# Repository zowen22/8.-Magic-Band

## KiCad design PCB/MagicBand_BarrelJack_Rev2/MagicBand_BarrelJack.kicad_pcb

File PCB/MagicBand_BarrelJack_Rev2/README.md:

# MagicBand_BarrelJack — Revision 2

*Created: 2026-10-13. Copied from `PCB/MagicBand_BarrelJack/` (rev 1, fab-ready, two boards fabricated/assembled and in bring-up) — that folder stays untouched/frozen as the as-fabricated reference. This folder is where rev 2 design changes happen.*

Only the KiCad source files were copied (`.kicad_pro/.kicad_sch/.kicad_pcb/.kicad_prl`) — not rev 1's BOM/CPL/gerbers/SVGs/DRC-ERC reports, since those are rev 1-specific fab outputs that would be misleading here until rev 2 actually has changes and gets its own export pass.

## Scope (decided 2026-10-13)

Cleanup pass on the existing wall-powered architecture **plus** a real second-LED-strip connector. **Not** a revisit of the paused battery-powered/IRQ-wake variant — that stays paused pending its own separate decision (see `2. Project Overview.md` Decisions Log, 2026-08-04 entry).

## Backlog — see `3. Work Packages.md` WP4.3 for the authoritative, maintained list

Summary as of creation (check WP4.3 directly for current status, don't trust this snapshot):
1. Silkscreen: per-pin signal labels near J2/J3/J8/J9
2. J6 wire-color documentation/sourcing fix (pigtail kit colors inverted from NeoPixel convention)
3. J6 pin order vs. actual LED strip pad order
4. J8 through-hole size vs. actual barrel-jack wire gauge
5. **New, real connector for second LED strip** (rev 1 only has a hand-bodged wire to U1's D2 leg + a J8 power tap — see `Build Instructions - Barrel-Jack Variant.md` Step 5a — rev 2 should give this its own header + proper trace sizing, not a bodge)
6. +5V trace width to the LED strip(s) — rev 1's 0.2mm trunk sizing was a judgment call, not computed from hard math; revisit with real numbers once rev 2's actual LED part (a new, smaller/lower-draw 2.7mm-width LED, BOM link pending from @user) is confirmed, especially now that it's feeding two strips instead of one
7. RF antenna/J3 keepout — only fix if board 1/2 testing actually shows reduced 433MHz range, don't fix pre-emptively
8. Cosmetic-only: R1/Y1 silkscreen overlap, 3 starved-thermal pour-island flags — bundle in only if doing a placement pass anyway

## What's NOT done yet

No schematic/PCB edits have been made in this folder — it's an exact copy of rev 1 as of 2026-10-13. Placement/routing/silkscreen work in this project has always been a GUI + user session (see `4. Technical Reference.md`'s FreeRouting/placement workflow), not something done headlessly — next step is a live KiCad session against this folder once the second-strip connector's footprint/pin-out is picked.

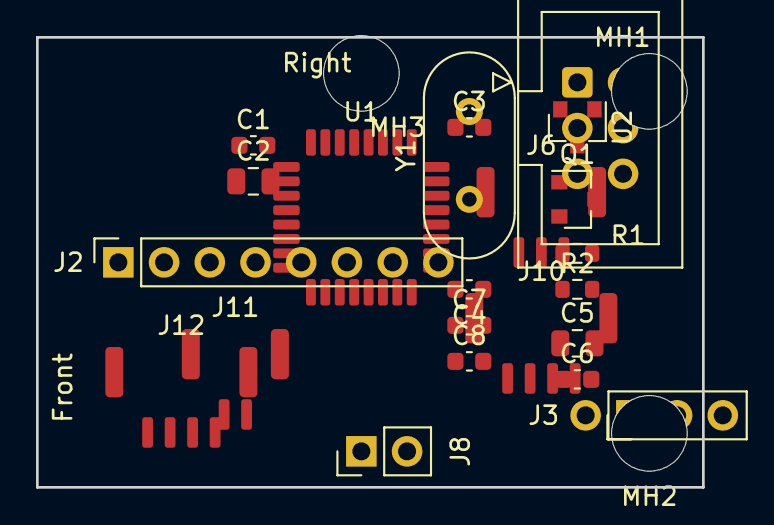
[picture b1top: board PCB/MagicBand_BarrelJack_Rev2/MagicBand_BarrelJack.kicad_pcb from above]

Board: 2 copper layers, 37.0 x 25.0 mm, 25 parts (0 on the bottom side), 22 nets, no tracks yet.

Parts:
C1, C3, C4, C6, C7, C8: C_0603_1608Metric
C2, C5: C_0805_2012Metric
J2: PinSocket_1x08_P2.54mm_Vertical
J3: PinHeader_1x04_P2.54mm_Vertical
J6: LED_OUTER_RING_3P; JST_GH_BM03B-GHS-TBT_1x03-1MP_P1.25mm_Vertical
J8: PinHeader_1x02_P2.54mm_Vertical
J9: IDC-Header_2x03_P2.54mm_Vertical
J10: LED_INNER_RING_4P; JST_GH_BM04B-GHS-TBT_1x04-1MP_P1.25mm_Vertical
J11: SWITCH_2P; JST_GH_BM02B-GHS-TBT_1x02-1MP_P1.25mm_Vertical
J12: SPARE_BREAKOUT_4P; JST_GH_BM04B-GHS-TBT_1x04-1MP_P1.25mm_Vertical
MH1, MH2, MH3: MountingHole_4.2mm
Q1: SOT-23
R1, R2: R_0603_1608Metric
U1: ATmega328P-A; TQFP-32_7x7mm_P0.8mm
U2: SOT-23
Y1: Crystal_HC49-4H_Vertical

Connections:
+3V3: C7.1, J2.8, J3.2, U2.2
+5V: C3.1, C4.1, C5.1, C6.1, J6.1, J9.2, J10.1, Q1.3, R1.1, U1.4, U1.6, U1.18, U2.3
D2: J10.3, U1.32
D4: J2.1, U1.2
D5: J6.3, U1.9
D7: J12.1, U1.11
D8: J3.1, U1.12
D9: J2.7, U1.13
D10: J12.2, U1.14
D11: J2.3, J9.4, U1.15
D12: J2.4, J9.1, U1.16
D13: J2.2, J9.3, U1.17
GND: C1.2, C2.2, C3.2, C4.2, C5.2, C6.2, C7.2, C8.2, J2.6, J3.3, J6.2, J8.2, J9.6, J10.2, J11.2, R2.2, U1.3, U1.5, U1.21, U2.1
MCU_RESET: J9.5, R1.2, U1.29
unnamed: J8.1, Q1.2
unnamed: Q1.1, R2.1
unnamed: C8.1, U1.20
unnamed: C1.1, U1.7, Y1.1
unnamed: C2.1, U1.8, Y1.2
RXD: J12.3, U1.30
SWITCH: J11.1, U1.1
TXD: J12.4, U1.31

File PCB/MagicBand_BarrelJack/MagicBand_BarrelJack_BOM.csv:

"Refs","Value","Footprint","Qty","DNP"
"C1","27pF","Capacitor_SMD:C_0603_1608Metric","1",""
"C2","27pF","Capacitor_SMD:C_0805_2012Metric","1",""
"C3,C4,C8","100nF","Capacitor_SMD:C_0603_1608Metric","3",""
"C5","1uF","Capacitor_SMD:C_0805_2012Metric","1",""
"C6","10uF","Capacitor_SMD:C_0603_1608Metric","1",""
"C7","1.0uF","Capacitor_SMD:C_0603_1608Metric","1",""
"J2","MFRC522_Module","Connector_PinSocket_2.54mm:PinSocket_1x08_P2.54mm_Vertical","1",""
"J3","RF_TX_DFLIFE","Connector_PinHeader_2.54mm:PinHeader_1x04_P2.54mm_Vertical","1","DNP"
"J6","NeoPixel_LED_Strip","Connector_JST:JST_PH_B3B-PH-K_1x03_P2.00mm_Vertical","1",""
"J8","PWR_IN_BarrelJack_BareLeads","Connector_PinHeader_2.54mm:PinHeader_1x02_P2.54mm_Vertical","1","DNP"
"J9","ISP_AVR_2x3","Connector_IDC:IDC-Header_2x03_P2.54mm_Vertical","1",""
"Q1","AO3401A_PMOS_G-S-D","Package_TO_SOT_SMD:SOT-23","1",""
"R1,R2","10k","Resistor_SMD:R_0603_1608Metric","2",""
"U1","ATmega328P-P","Package_DIP:DIP-28_W7.62mm","1",""
"U2","MCP1700-3302","Package_TO_SOT_SMD:SOT-23","1",""
"Y1","16MHz","Crystal:Crystal_HC49-4H_Vertical","1",""

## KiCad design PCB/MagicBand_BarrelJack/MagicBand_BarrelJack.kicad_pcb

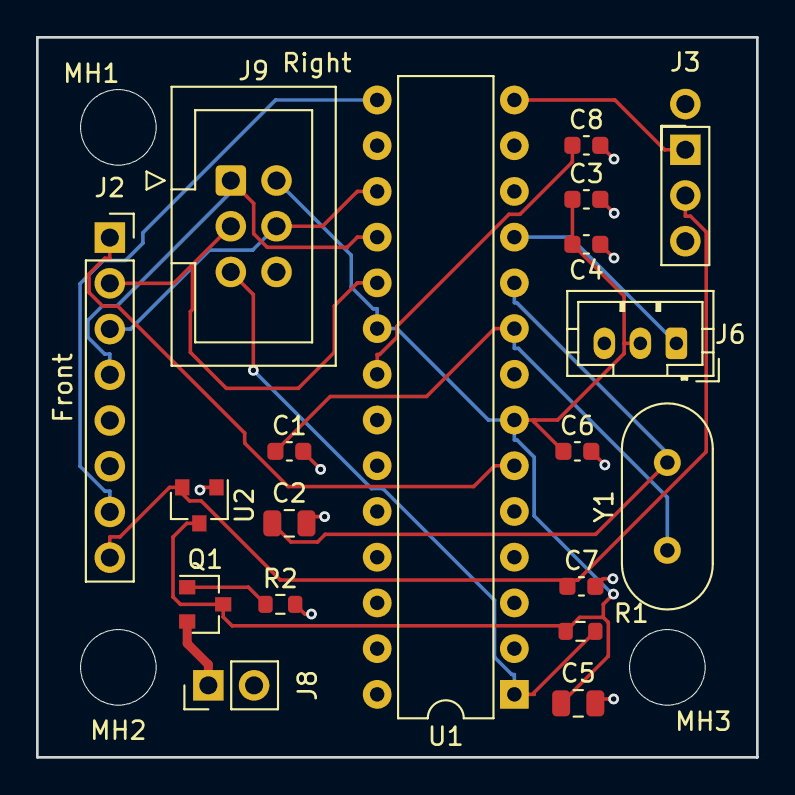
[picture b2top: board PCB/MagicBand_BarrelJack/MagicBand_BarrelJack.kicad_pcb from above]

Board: 2 copper layers, 40.0 x 40.0 mm, 22 parts (0 on the bottom side), 16 nets.

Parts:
C1, C3, C4, C6, C7, C8: C_0603_1608Metric
C2, C5: C_0805_2012Metric
J2: PinSocket_1x08_P2.54mm_Vertical
J3: PinHeader_1x04_P2.54mm_Vertical
J6: JST_PH_B3B-PH-K_1x03_P2.00mm_Vertical
J8: PinHeader_1x02_P2.54mm_Vertical
J9: IDC-Header_2x03_P2.54mm_Vertical
MH1, MH2, MH3: MountingHole_4.2mm
Q1: SOT-23
R1, R2: R_0603_1608Metric
U1: DIP-28_W7.62mm
U2: SOT-23
Y1: Crystal_HC49-4H_Vertical

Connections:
+3V3: C7.1, J2.8, J3.2, U2.2
+5V: C3.1, C4.1, C5.1, C6.1, J6.2, J9.2, Q1.3, R1.1, U1.7, U1.20, U2.3
D4: J2.1, U1.6
D5: J6.1, U1.11
D8: J3.1, U1.14
D9: J2.7, U1.15
D11: J2.3, J9.4, U1.17
D12: J2.4, J9.1, U1.18
D13: J2.2, J9.3, U1.19
GND: C1.2, C2.2, C3.2, C4.2, C5.2, C6.2, C7.2, C8.2, J2.6, J3.3, J6.3, J8.2, J9.6, R2.2, U1.8, U1.22, U2.1
MCU_RESET: J9.5, R1.2, U1.1
unnamed: J8.1, Q1.2
unnamed: Q1.1, R2.1
unnamed: C8.1, U1.21
unnamed: C1.1, U1.9, Y1.1
unnamed: C2.1, U1.10, Y1.2

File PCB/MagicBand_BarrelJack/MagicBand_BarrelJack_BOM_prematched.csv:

"Designator","Comment","Footprint","JLCPCB Part #","Qty","DNP"
"C1","27pF","Capacitor_SMD:C_0603_1608Metric","C107045","1",""
"C2","27pF","Capacitor_SMD:C_0805_2012Metric","C1808","1",""
"C3,C4,C8","100nF","Capacitor_SMD:C_0603_1608Metric","C14663","3",""
"C5","1uF","Capacitor_SMD:C_0805_2012Metric","C28323","1",""
"C6","10uF","Capacitor_SMD:C_0603_1608Metric","C19702","1",""
"C7","1.0uF","Capacitor_SMD:C_0603_1608Metric","C15849","1",""
"J2","MFRC522_Module","Connector_PinSocket_2.54mm:PinSocket_1x08_P2.54mm_Vertical","","1","DNP"
"J3","RF_TX_DFLIFE","Connector_PinHeader_2.54mm:PinHeader_1x04_P2.54mm_Vertical","","1","DNP"
"J6","NeoPixel_LED_Strip","Connector_JST:JST_PH_B3B-PH-K_1x03_P2.00mm_Vertical","C158004","1",""
"J8","PWR_IN_BarrelJack_BareLeads","Connector_PinHeader_2.54mm:PinHeader_1x02_P2.54mm_Vertical","","1","DNP"
"J9","ISP_AVR_2x3","Connector_IDC:IDC-Header_2x03_P2.54mm_Vertical","C492441","1",""
"Q1","AO3401A_PMOS_G-S-D","Package_TO_SOT_SMD:SOT-23","C15127","1",""
"R1,R2","10k","Resistor_SMD:R_0603_1608Metric","C25804","2",""
"U1","ATmega328P-P","Package_DIP:DIP-28_W7.62mm","C33901","1",""
"U2","MCP1700-3302","Package_TO_SOT_SMD:SOT-23","C41381676","1",""
"Y1","16MHz","Crystal:Crystal_HC49-4H_Vertical","C295075","1",""
